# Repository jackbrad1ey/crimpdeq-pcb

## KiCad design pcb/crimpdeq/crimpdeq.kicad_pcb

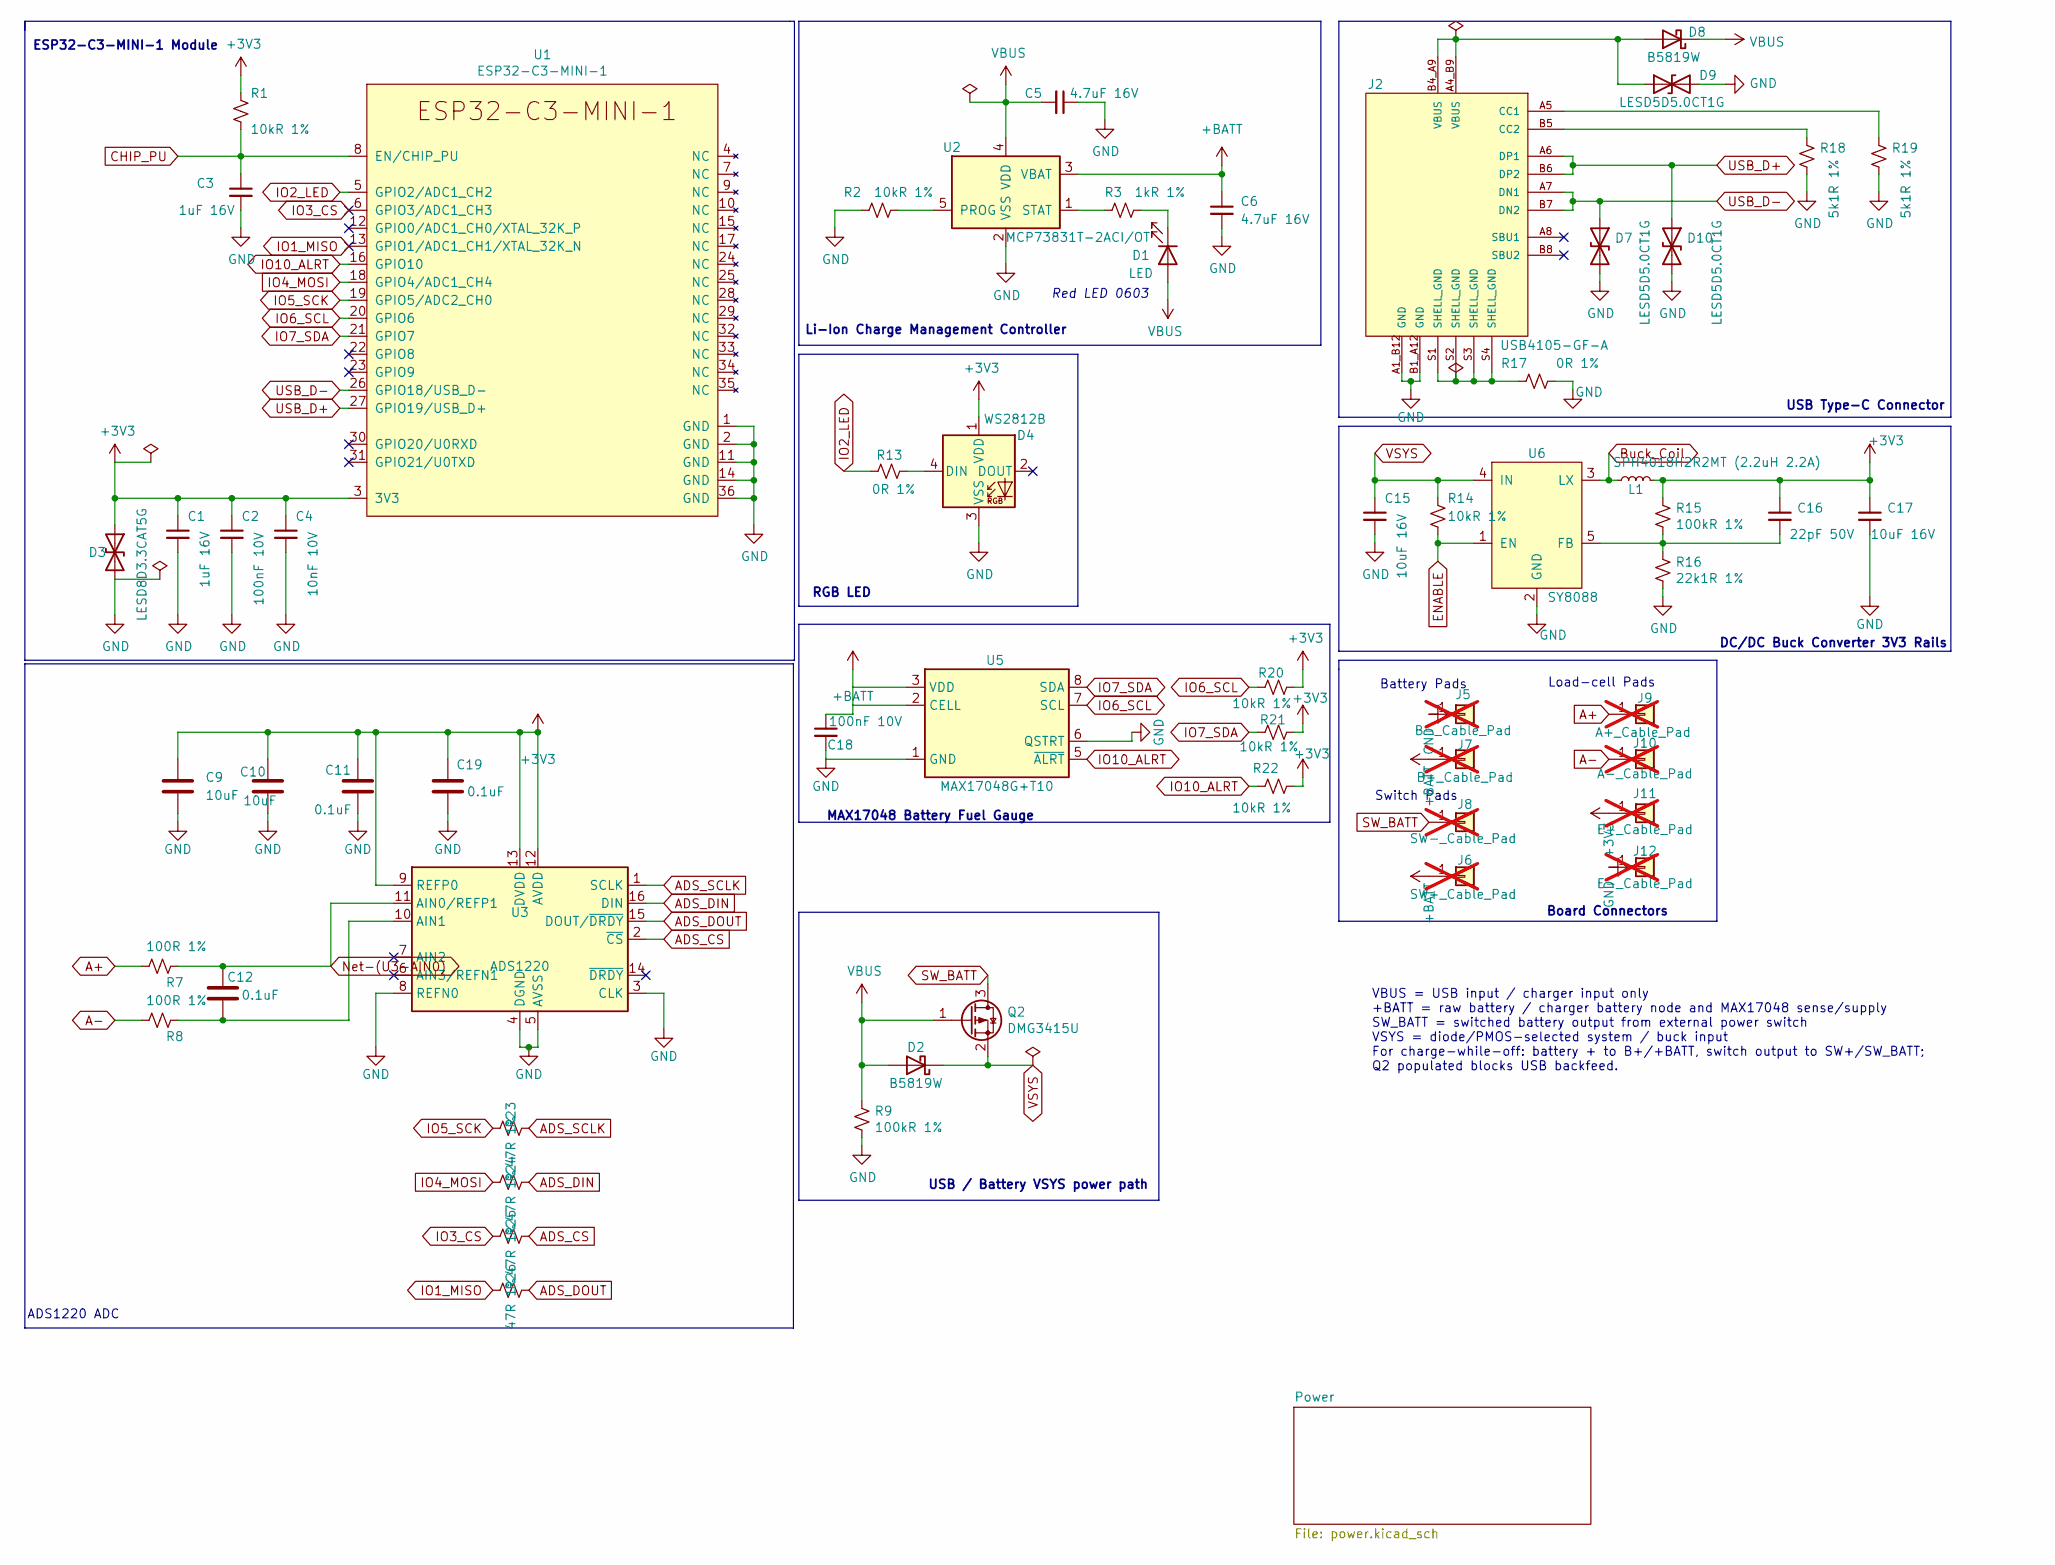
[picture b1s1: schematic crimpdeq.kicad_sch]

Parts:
C1, C3: 1uF 16V; C_0402_1005Metric; LCSC C52923
C2: 100nF 10V; C_0402_1005Metric; LCSC C1525
C4: 10nF 10V; C_0402_1005Metric; LCSC C15195
C5, C6: 4.7uF 16V; C_0603_1608Metric; LCSC C19666
C9, C10: 10uF; C_0603_1608Metric
C11, C19: 0.1uF; C_0603_1608Metric
C12: 0.1uF; C_1206_3216Metric; MPN GRM31C5C2A104JA01L; LCSC C405303
C15, C17: 10uF 16V; C_0805_2012Metric; LCSC C15850
C16: 22pF 50V; C_0603_1608Metric; LCSC C1653
C18: 100nF 10V; C_0402_1005Metric
D1: LED; LED_0603_1608Metric; LCSC C2286
D2, D8: B5819W; D_SOD-123; LCSC C8598
D3: LESD8D3.3CAT5G; D_SOD-882; LCSC C172409
D4: WS2812B; LED_WS2812B_PLCC4_5.0x5.0mm_P3.2mm; MPN WS2812B-V6; LCSC C52917433
D7, D9, D10: LESD5D5.0CT1G; D_SOD-523; LCSC C383211
J2: USB4105-GF-A; GCT_USB4105-GF-A; PARTREV A3; LCSC C165948
J5: B-_Cable_Pad; TestPoint_THTPad_D1.5mm_Drill0.7mm; not fitted
J6: SW+_Cable_Pad; TestPoint_THTPad_D1.5mm_Drill0.7mm; not fitted
J7: B+_Cable_Pad; TestPoint_THTPad_D1.5mm_Drill0.7mm; not fitted
J8: SW-_Cable_Pad; TestPoint_THTPad_D1.5mm_Drill0.7mm; not fitted
J9: A+_Cable_Pad; TestPoint_THTPad_D1.5mm_Drill0.7mm; not fitted
J10: A-_Cable_Pad; TestPoint_THTPad_D1.5mm_Drill0.7mm; not fitted
J11: E+_Cable_Pad; TestPoint_THTPad_D1.5mm_Drill0.7mm; not fitted
J12: E-_Cable_Pad; TestPoint_THTPad_D1.5mm_Drill0.7mm; not fitted
L1: SPH4018H2R2MT (2.2uH 2.2A); L_Bourns-SRN4018; LCSC C370436
Q2: DMG3415U; SOT-23; MPN DMG3415U-7; LCSC C96616
R1, R2, R14: 10kR 1%; R_0402_1005Metric; LCSC C25744
R3: 1kR 1%; R_0402_1005Metric; LCSC C11702
R7, R8: 100R 1%; R_0402_1005Metric; LCSC C25076
R9, R15: 100kR 1%; R_0402_1005Metric; LCSC C25741
R13: 0R 1%; R_0402_1005Metric; LCSC C25744
R16: 22k1R 1%; R_0402_1005Metric; LCSC C43473
R17: 0R 1%; R_0402_1005Metric; LCSC C17168
R18, R19: 5k1R 1%; R_0402_1005Metric; LCSC C25905
R20, R21, R22: 10kR 1%; R_0402_1005Metric; LCSC C60490
R23, R24, R25, R26: 47R 1%; R_0402_1005Metric; MPN 0402WGF470JTCE; LCSC C25118
U1: ESP32-C3-MINI-1; MPN ESP32-C3-MINI-1; LCSC C2838502
U2: MCP73831T-2ACI/OT; MCP73831_SOT-23-5; LCSC C424093
U3: ADS1220; TSSOP-16_4.4x5mm_P0.65mm; MPN ADS1220IPWR; LCSC C48263
U5: MAX17048G+T10; TDFN-8-1EP_2x2mm_P0.5mm_EP0.8x1.2mm; MPN MAX17048G+T10; LCSC C2682616
U6: SY8088; SY8088_SOT-23-5; LCSC C479072

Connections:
+3V3: C1.1, C2.1, C4.1, C9.1, C10.1, C11.1, C16.1, C17.1, C19.1, D3.1 (A1), D4.1 (VDD), J11.1 (Pin_1_1), L1.2, R1.1, R15.1, R20.2, R21.2, R22.2, U1.3 (3V3), U3.9 (REFP0), U3.12 (AVDD), U3.13 (DVDD); also elsewhere on the board
+BATT: C6.1, C18.1, J6.1 (Pin_1_1), J7.1 (Pin_1_1), U2.3 (VBAT), U5.2 (CELL), U5.3 (VDD); also elsewhere on the board
A+: J9.1 (Pin_1_1), R7.2
A-: J10.1 (Pin_1_1), R8.2
ADS_CS: R25.2, U3.2 (~CS)
ADS_DIN: R24.2, U3.16 (DIN)
ADS_DOUT: R26.1, U3.15 (DOUT/~DRDY)
ADS_SCLK: R23.2, U3.1 (SCLK)
Buck_Coil: L1.1, U6.3 (LX)
CHIP_PU: C3.1, R1.2, U1.8 (EN/CHIP_PU)
ENABLE: R14.2, U6.1 (EN)
GND: C1.2, C2.2, C3.2, C4.2, C5.1, C6.2, C9.2, C10.2, C11.2, C15.2, C17.2, C18.2, C19.2, D3.2 (A2), D4.3 (VSS), D7.2 (A2), D9.2 (A2), D10.2 (A2), J2.A1_B12 (GND), J2.B1_A12 (GND), J5.1 (Pin_1_1), J12.1 (Pin_1_1), R2.1, R9.2, R16.2, R17.2, R18.2, R19.2, U1.1 (GND), U1.2 (GND), U1.11 (GND), U1.14 (GND), U1.36 (GND), U1.37 (GND), U1.38 (GND), U1.39 (GND), U1.40 (GND), U1.41 (GND), U1.42 (GND), U1.43 (GND), U1.44 (GND), U1.45 (GND), U1.46 (GND), U1.47 (GND), U1.48 (GND), U1.49 (GND), U1.50 (GND), U1.51 (GND), U1.52 (GND), U1.53 (GND), U2.2 (VSS), U3.3 (CLK), U3.4 (DGND), U3.5 (AVSS), U3.8 (REFN0), U5.1 (GND), U5.4 (GND), U5.6 (QSTRT), U5.9 (GND), U6.2 (GND); also elsewhere on the board
IO1_MISO: R26.2, U1.13 (GPIO1/ADC1_CH1/XTAL_32K_N)
IO2_LED: R13.1, U1.5 (GPIO2/ADC1_CH2)
IO3_CS: R25.1, U1.6 (GPIO3/ADC1_CH3)
IO4_MOSI: R24.1, U1.18 (GPIO4/ADC1_CH4)
IO5_SCK: R23.1, U1.19 (GPIO5/ADC2_CH0)
IO6_SCL: R20.1, U1.20 (GPIO6), U5.7 (SCL)
IO7_SDA: R21.1, U1.21 (GPIO7), U5.8 (SDA)
IO10_ALRT: R22.1, U1.16 (GPIO10), U5.5 (~ALRT)
unnamed: D1.1 (K), R3.2
unnamed: D4.4 (DIN), R13.2
unnamed: D8.2 (A), D9.1 (A1), J2.A4_B9 (VBUS), J2.B4_A9 (VBUS)
unnamed: J2.A5 (CC1), R19.1
unnamed: J2.B5 (CC2), R18.1
unnamed: J2.S1 (SHELL_GND), J2.S2 (SHELL_GND), J2.S3 (SHELL_GND), J2.S4 (SHELL_GND), R17.1
unnamed: R2.2, U2.5 (PROG)
unnamed: R3.1, U2.1 (STAT)
unnamed: C12.1, R7.1, U3.11 (AIN0/REFP1)
unnamed: C12.2, R8.1, U3.10 (AIN1)
unnamed: C16.2, R15.2, R16.1, U6.5 (FB)
SW_BATT: J8.1 (Pin_1_1), Q2.3 (D); also elsewhere on the board
USB_D+: D10.1 (A1), J2.A6 (DP1), J2.B6 (DP2), U1.27 (GPIO19/USB_D+)
USB_D-: D7.1 (A1), J2.A7 (DN1), J2.B7 (DN2), U1.26 (GPIO18/USB_D-)
VBUS: C5.2, D1.2 (A), D2.2 (A), D8.1 (K), Q2.1 (G), R9.1, U2.4 (VDD); also elsewhere on the board
VSYS: C15.1, D2.1 (K), Q2.2 (S), R14.1, U6.4 (IN); also elsewhere on the board

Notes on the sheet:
ADS1220 ADC
USB Type-C Connector
Board Connectors
Li-Ion Charge Management Controller
USB / Battery VSYS power path
MAX17048 Battery Fuel Gauge
Red LED 0603
Load-cell Pads
Switch Pads
ESP32-C3-MINI-1 Module
RGB LED
DC/DC Buck Converter 3V3 Rails
Battery Pads
VBUS = USB input / charger input only +BATT = raw battery / charger battery node and MAX17048 sense/supply SW_BATT = switched battery output from external power switch VSYS = diode/PMOS-selected system / buck input For charge-while-off: battery + to B+/+BATT, switch output to SW+/SW_BATT; Q2 popula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

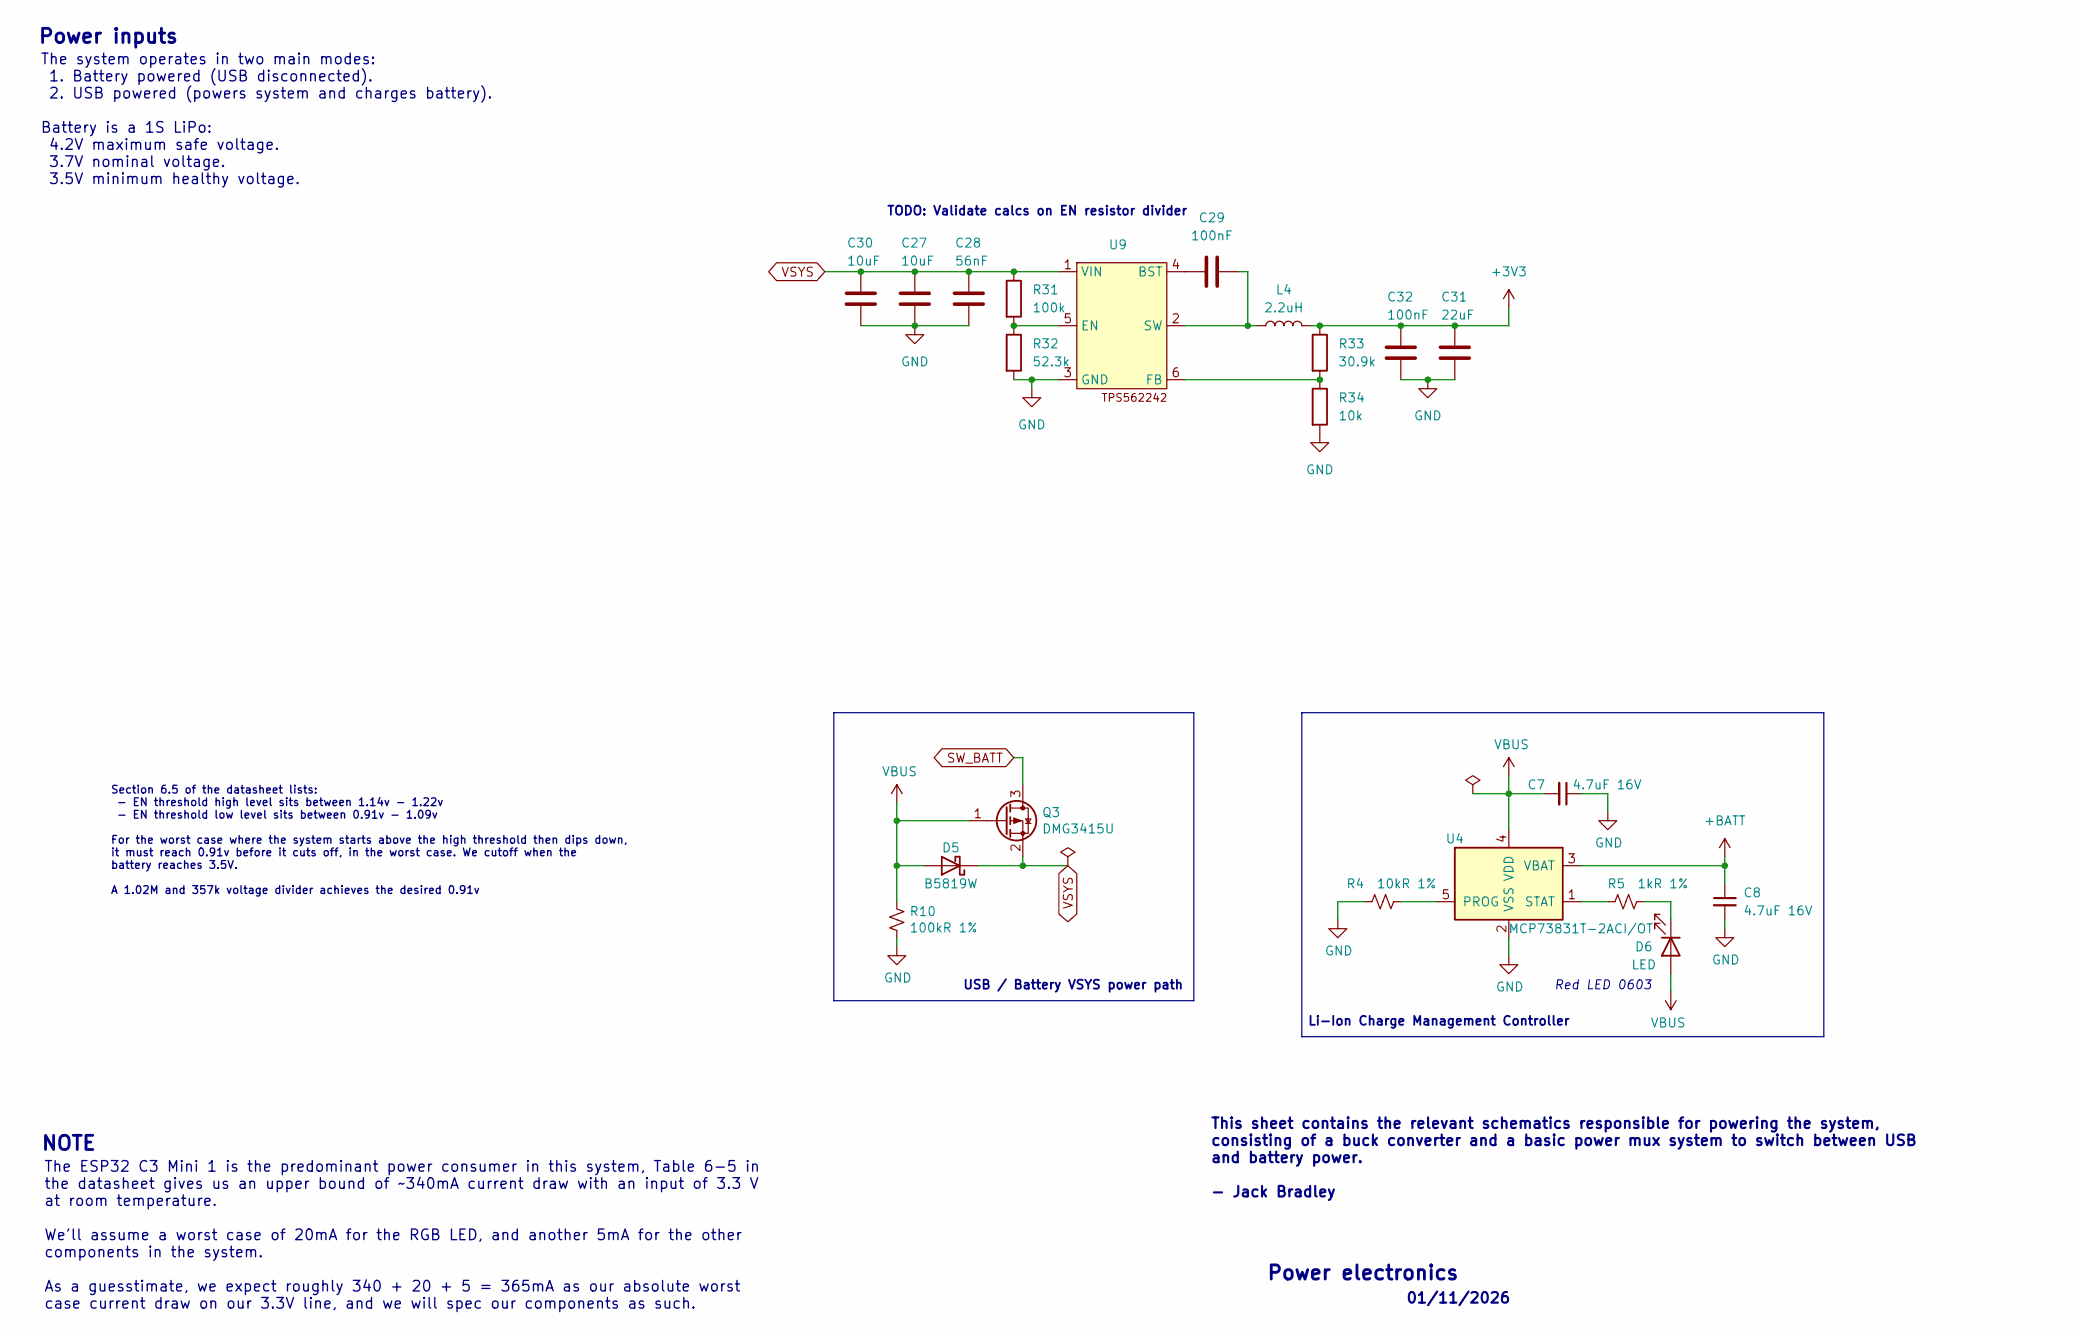
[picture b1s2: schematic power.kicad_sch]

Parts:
C7, C8: 4.7uF 16V; C_0603_1608Metric; LCSC C19666
C27, C30: 10uF; C_0603_1608Metric
C28: 56nF; C_0402_1005Metric
C29, C32: 100nF; C_0402_1005Metric
C31: 22uF; C_0805_2012Metric; LCSC C318688
D5: B5819W; D_SOD-123; LCSC C8598
D6: LED; LED_0603_1608Metric; LCSC C2286
L4: 2.2uH; L_1210_3225Metric; LCSC C49490367
Q3: DMG3415U; SOT-23; MPN DMG3415U-7; LCSC C96616
R4: 10kR 1%; R_0402_1005Metric; LCSC C25744
R5: 1kR 1%; R_0402_1005Metric; LCSC C11702
R10: 100kR 1%; R_0402_1005Metric; LCSC C25741
R31: 100k; R_0402_1005Metric
R32: 52.3k; R_0402_1005Metric
R33: 30.9k; R_0402_1005Metric
R34: 10k; R_0402_1005Metric
U4: MCP73831T-2ACI/OT; MCP73831_SOT-23-5; LCSC C424093
U9: SOT-563

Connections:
+3V3: C31.1, C32.2, L4.2, R33.1; also elsewhere on the board
+BATT: C8.1, U4.3 (VBAT); also elsewhere on the board
GND: C7.1, C8.2, C27.2, C28.1, C30.2, C31.2, C32.1, R4.1, R10.2, R32.2, R34.2, U4.2 (VSS), U9.3 (GND); also elsewhere on the board
unnamed: D6.1 (K), R5.2
unnamed: R4.2, U4.5 (PROG)
unnamed: R5.1, U4.1 (STAT)
unnamed: C29.1, U9.4 (BST)
unnamed: R31.2, R32.1, U9.5 (EN)
unnamed: R33.2, R34.1, U9.6 (FB)
unnamed: C29.2, L4.1, U9.2 (SW)
SW_BATT: Q3.3 (D); also elsewhere on the board
VBUS: C7.2, D5.2 (A), D6.2 (A), Q3.1 (G), R10.1, U4.4 (VDD); also elsewhere on the board
VSYS: C27.1, C28.2, C30.1, D5.1 (K), Q3.2 (S), R31.1, U9.1 (VIN); also elsewhere on the board

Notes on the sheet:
Red LED 0603
Li-Ion Charge Management Controller
This sheet contains the relevant schematics responsible for powering the system, consisting of a buck converter and a basic power mux system to switch between USB and battery power. - Jack Bradley
Power inputs
The ESP32 C3 Mini 1 is the predominant power consumer in this system, Table 6-5 in the datasheet gives us an upper bound of ~340mA current draw with an input of 3.3 V at room temperature. We'll assume a worst case of 20mA for the RGB LED, and another 5mA for the other components in the system. As a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
Power electronics
TODO: Validate calcs on EN resistor divider
The system operates in two main modes: 1. Battery powered (USB disconnected). 2. USB powered (powers system and charges battery). Battery is a 1S LiPo: 4.2V maximum safe voltage. 3.7V nominal voltage. 3.5V minimum healthy voltage.
Section 6.5 of the datasheet lists: - EN threshold high level sits between 1.14v - 1.22v - EN threshold low level sits between 0.91v - 1.09v For the worst case where the system starts above the high threshold then dips down, it must reach 0.91v before it cuts off, in the worst case. We cutoff when 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
USB / Battery VSYS power path
NOTE
01/11/2026

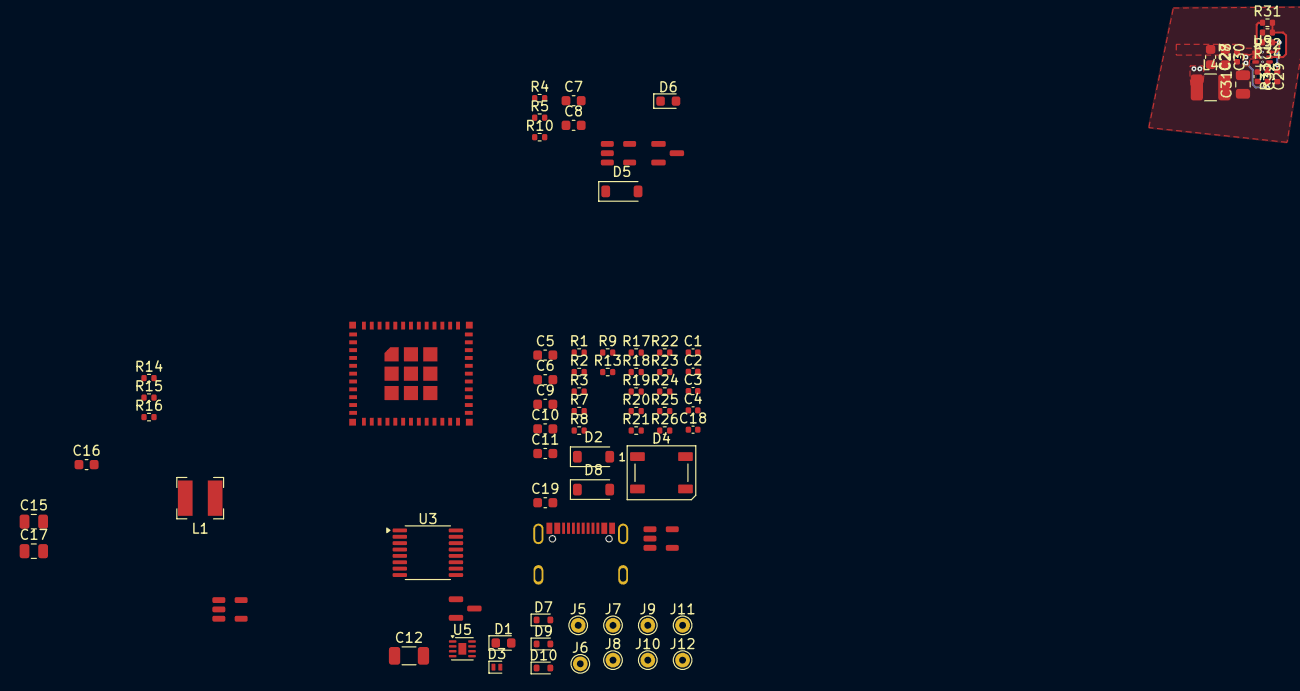
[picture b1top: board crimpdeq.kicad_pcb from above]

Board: 2 copper layers, 80 parts (0 on the bottom side), 43 nets.
